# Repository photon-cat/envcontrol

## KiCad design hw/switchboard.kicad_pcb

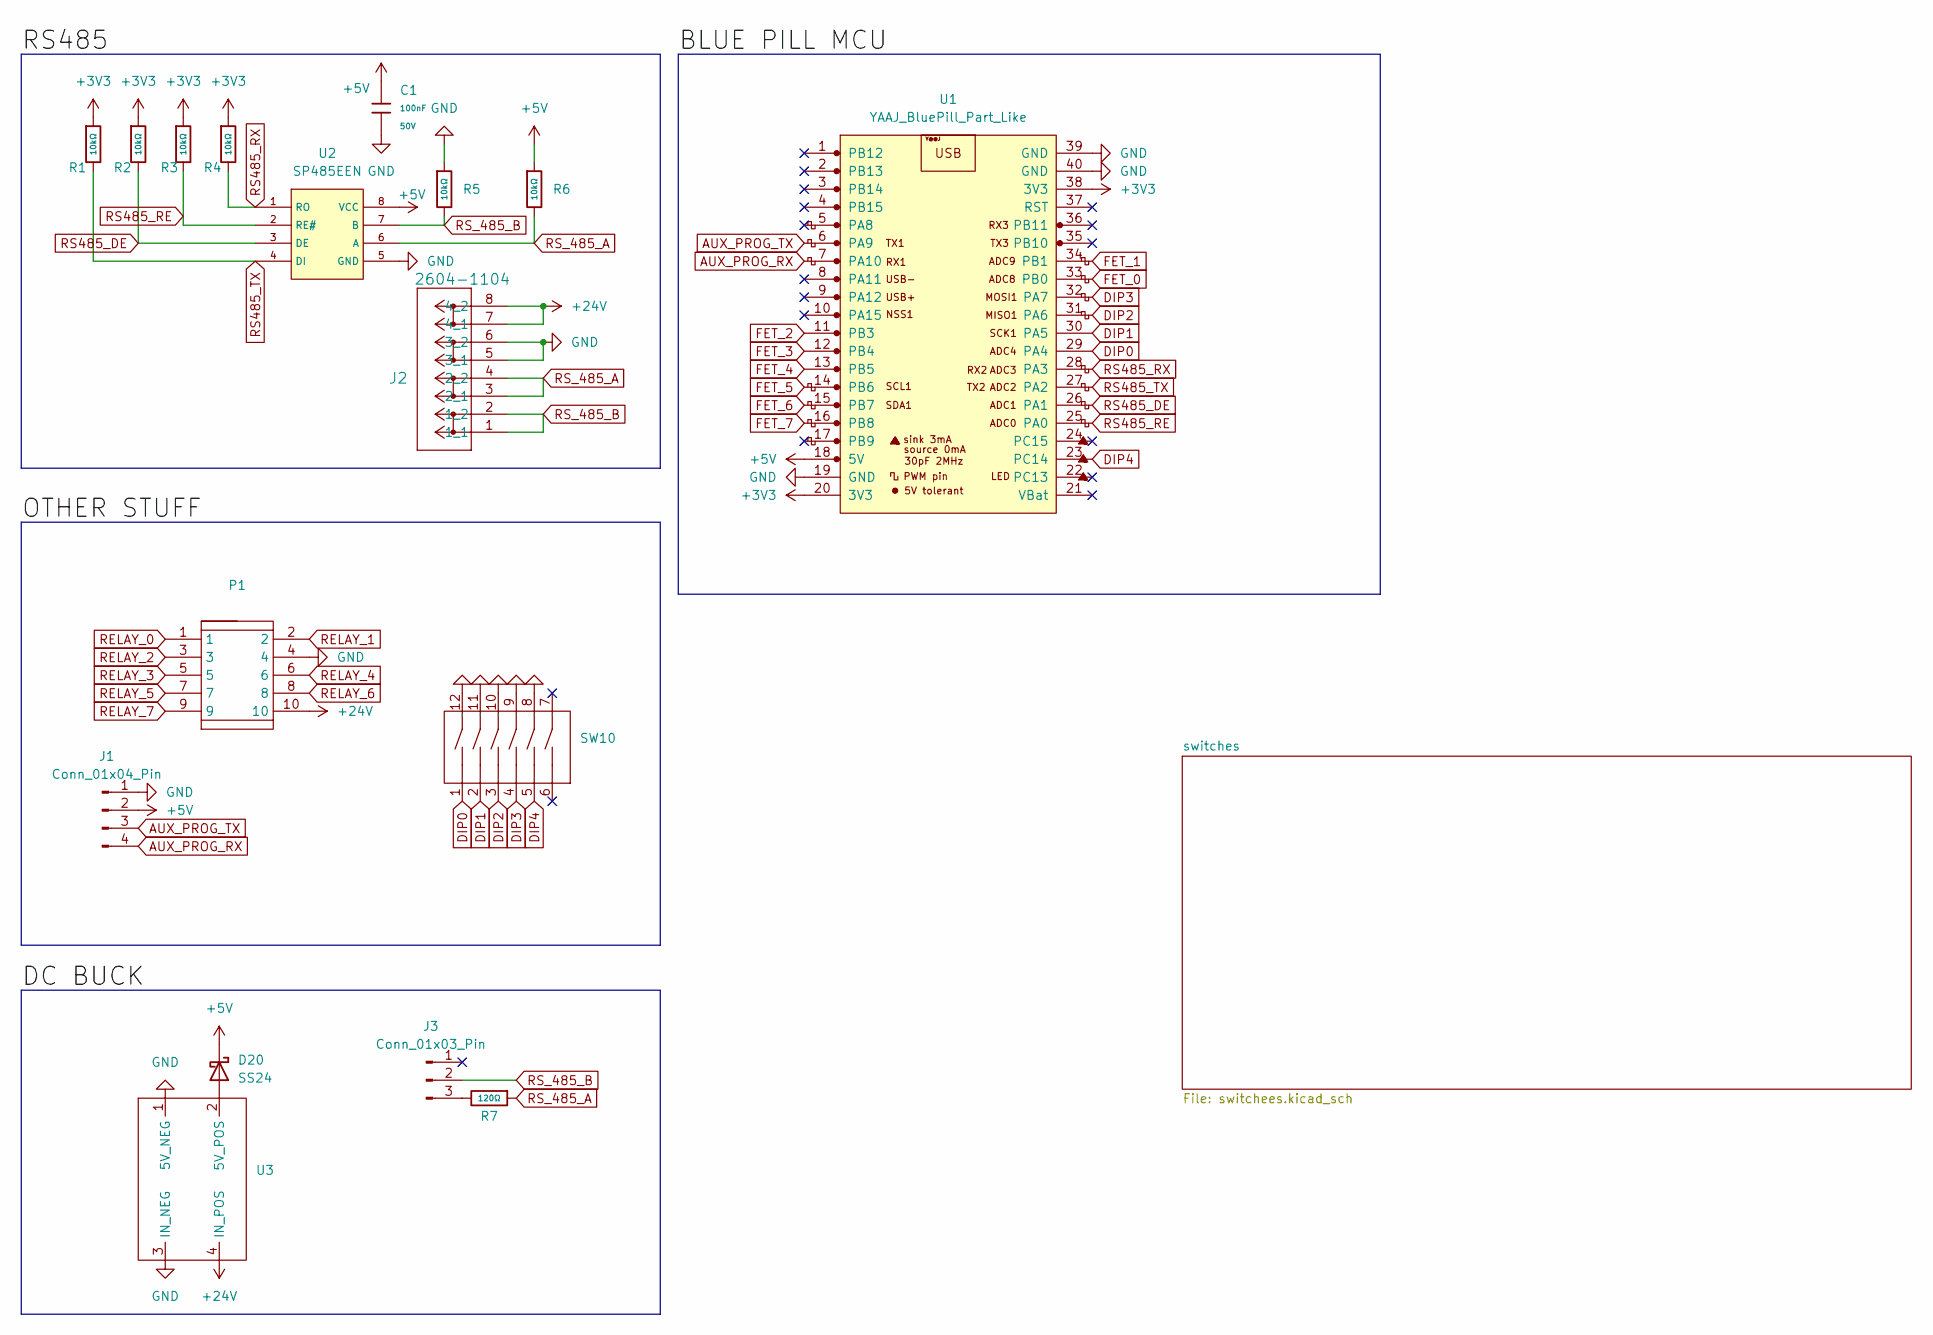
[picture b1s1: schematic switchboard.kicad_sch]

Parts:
C1: 100nF; C_0603; Voltage Rated 50V; Tolerance ±10%; Part CC0603KRX7R9BB104; LCSC C14663
D20: SS24; D_SMA
J1: Conn_01x04_Pin; PinHeader_1x04_P2.54mm_Vertical
J2: 2604-1104; CONN4_2604-1104_WAG
J3: Conn_01x03_Pin; PinHeader_1x03_P2.54mm_Horizontal
P1: IDC-TH_10P-P2.54-H-R2-C5-S2.54; Manufacturer Part 2.54-2*5P弯简牛; LCSC Part Name 2.54mm 2x5P 排数:2 每排P数:5
R1, R2, R3, R4, R5, R6: 10kΩ; R_0603; Overload Voltage (Max) 75V; Tolerance ±1%; Part 0603WAF1002T5E; LCSC C25804
R7: 120Ω; R_0603; Overload Voltage (Max) 75V; Tolerance ±1%; Part 0603WAF1200T5E; LCSC C22787
SW10: SW-TH_12P-P2.54_SMQP-06B-TP; Manufacturer Part SMQP-06B-TP; LCSC Part Name 间距2.54mm 琴键6位拨码开关
U1: YAAJ_BluePill_Part_Like; YAAJ_BluePill_1
U2: SP485EEN; SOIC-8_L5.0-W4.0-P1.27-LS6.0-BL; Supply Voltage 4.75V~5.25V; Part SP485EEN-L/TR; LCSC C6855
U3: CHINA_MP1584EN

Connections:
+3V3: R1.1, R2.1, R3.1, R4.1, U1.20 (3V3), U1.38 (3V3)
+5V: C1.1, D20.1 (K), J1.2, R6.1, U1.18 (5V), U2.8 (VCC); also elsewhere on the board
+24V: J2.7 (4_1), J2.8 (4_2), P1.10, U3.4 (IN_POS)
AUX_PROG_RX: J1.4, U1.7 (PA10)
AUX_PROG_TX: J1.3, U1.6 (PA9)
DIP0: SW10.1, U1.29 (PA4)
DIP1: SW10.2, U1.30 (PA5)
DIP2: SW10.3, U1.31 (PA6)
DIP3: SW10.4, U1.32 (PA7)
DIP4: SW10.5, U1.23 (PC14)
FET_0: U1.33 (PB0); also elsewhere on the board
FET_1: U1.34 (PB1); also elsewhere on the board
FET_2: U1.11 (PB3); also elsewhere on the board
FET_3: U1.12 (PB4); also elsewhere on the board
FET_4: U1.13 (PB5); also elsewhere on the board
FET_5: U1.14 (PB6); also elsewhere on the board
FET_6: U1.15 (PB7); also elsewhere on the board
FET_7: U1.16 (PB8); also elsewhere on the board
GND: C1.2, J1.1, J2.5 (3_1), J2.6 (3_2), P1.4, R5.1, SW10.8, SW10.9, SW10.10, SW10.11, SW10.12, U1.19 (GND), U1.39 (GND), U1.40 (GND), U2.5 (GND), U3.1 (5V_NEG), U3.3 (IN_NEG); also elsewhere on the board
unnamed: D20.2 (A), U3.2 (5V_POS)
unnamed: J3.3, R7.2
RELAY_0: P1.1; also elsewhere on the board
RELAY_1: P1.2; also elsewhere on the board
RELAY_2: P1.3; also elsewhere on the board
RELAY_3: P1.5; also elsewhere on the board
RELAY_4: P1.6; also elsewhere on the board
RELAY_5: P1.7; also elsewhere on the board
RELAY_6: P1.8; also elsewhere on the board
RELAY_7: P1.9; also elsewhere on the board
RS485_DE: R2.2, U1.26 (PA1), U2.3 (DE)
RS485_RE: R3.2, U1.25 (PA0), U2.2 (RE#)
RS485_RX: R4.2, U1.28 (PA3), U2.1 (RO)
RS485_TX: R1.2, U1.27 (PA2), U2.4 (DI)
RS_485_A: J2.3 (2_1), J2.4 (2_2), R6.2, R7.1, U2.6 (A)
RS_485_B: J2.1 (1_1), J2.2 (1_2), J3.2, R5.2, U2.7 (B)

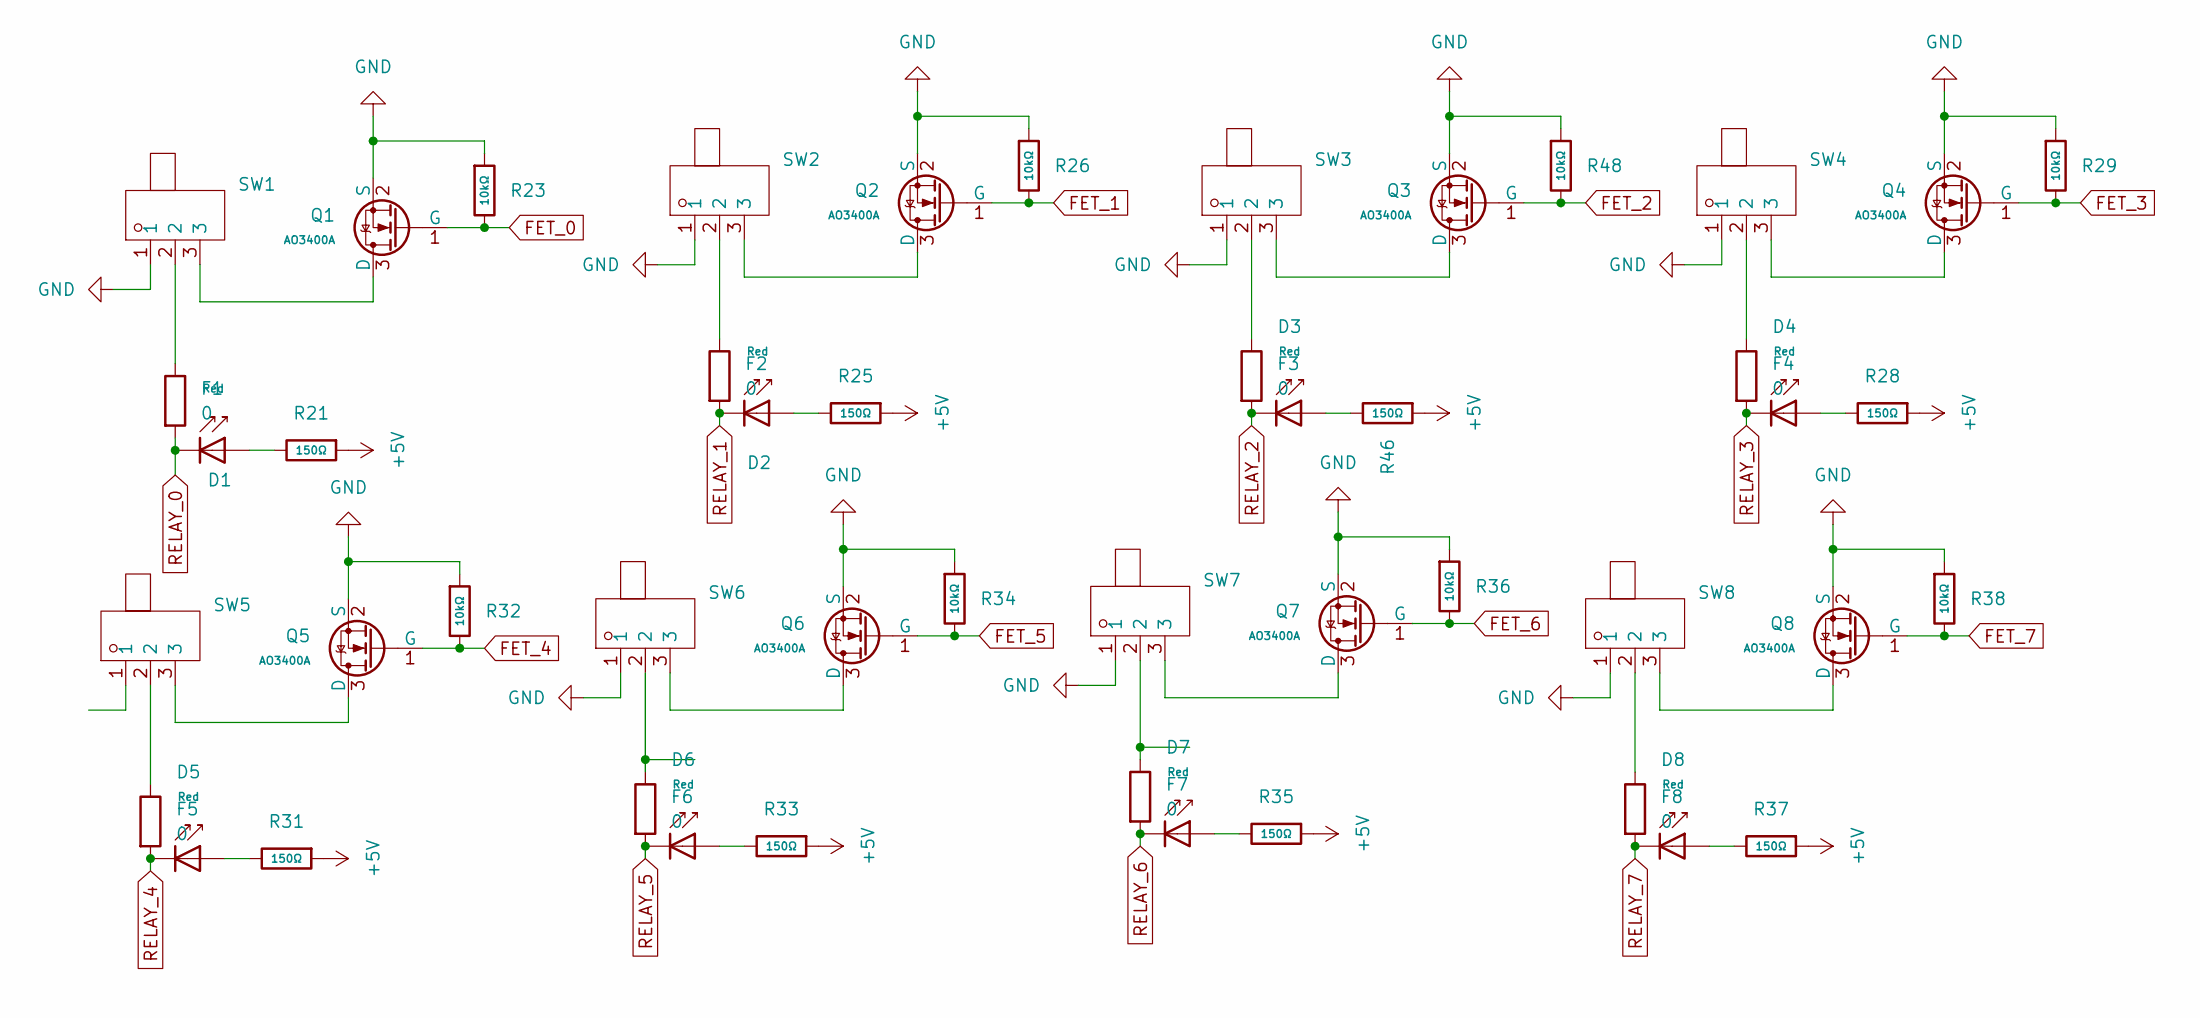
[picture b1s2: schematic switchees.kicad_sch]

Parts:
D1, D2, D3, D4, D5, D6, D7, D8: Red; D_0805; Forward Voltage (VF) 1.6V~2.6V; Part NCD0805R1; LCSC C84256
F1, F2, F3, F4, F5, F6, F7, F8: 0; R_0603
Q1, Q2, Q3, Q4, Q5, Q6, Q7, Q8: AO3400A; Q_SOT-23; Part AO3400A; LCSC C20917
R21, R25, R28, R31, R33, R35, R37, R46: 150Ω; R_0603; Overload Voltage (Max) 75V; Tolerance ±1%; Part 0603WAF1500T5E; LCSC C22808
R23, R26, R29, R32, R34, R36, R38, R48: 10kΩ; R_0603; Overload Voltage (Max) 75V; Tolerance ±1%; Part 0603WAF1002T5E; LCSC C25804
SW1, SW2, SW3, SW4, SW5, SW6, SW7, SW8: SW-TH_1MS1T1B1M1QES-5; Manufacturer Part 1MS1T1B1M1QES-5; LCSC Part Name 五件套 1MS1T1B1M1QES-5

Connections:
+5V: R21.1, R25.1, R28.1, R31.1, R33.1, R35.1, R37.1, R46.1; also elsewhere on the board
FET_0: Q1.1 (G), R23.2; also elsewhere on the board
FET_1: Q2.1 (G), R26.2; also elsewhere on the board
FET_2: Q3.1 (G), R48.2; also elsewhere on the board
FET_3: Q4.1 (G), R29.2; also elsewhere on the board
FET_4: Q5.1 (G), R32.2; also elsewhere on the board
FET_5: Q6.1 (G), R34.2; also elsewhere on the board
FET_6: Q7.1 (G), R36.2; also elsewhere on the board
FET_7: Q8.1 (G), R38.2; also elsewhere on the board
GND: Q1.2 (S), Q2.2 (S), Q3.2 (S), Q4.2 (S), Q5.2 (S), Q6.2 (S), Q7.2 (S), Q8.2 (S), R23.1, R26.1, R29.1, R32.1, R34.1, R36.1, R38.1, R48.1, SW1.1, SW2.1, SW3.1, SW4.1, SW6.1, SW7.1, SW8.1; also elsewhere on the board
unnamed: D1.2, R21.2
unnamed: D2.2, R25.2
unnamed: D3.2, R46.2
unnamed: D4.2, R28.2
unnamed: D5.2, R31.2
unnamed: D6.2, R33.2
unnamed: D7.2, R35.2
unnamed: D8.2, R37.2
unnamed: F1.1, SW1.2
unnamed: F2.1, SW2.2
unnamed: F3.1, SW3.2
unnamed: F4.1, SW4.2
unnamed: F5.1, SW5.2
unnamed: F6.1, SW6.2
unnamed: F7.1, SW7.2
unnamed: F8.1, SW8.2
unnamed: Q1.3 (D), SW1.3
unnamed: Q2.3 (D), SW2.3
unnamed: Q3.3 (D), SW3.3
unnamed: Q4.3 (D), SW4.3
unnamed: Q5.3 (D), SW5.3
unnamed: Q6.3 (D), SW6.3
unnamed: Q7.3 (D), SW7.3
unnamed: Q8.3 (D), SW8.3
RELAY_0: D1.1, F1.2; also elsewhere on the board
RELAY_1: D2.1, F2.2; also elsewhere on the board
RELAY_2: D3.1, F3.2; also elsewhere on the board
RELAY_3: D4.1, F4.2; also elsewhere on the board
RELAY_4: D5.1, F5.2; also elsewhere on the board
RELAY_5: D6.1, F6.2; also elsewhere on the board
RELAY_6: D7.1, F7.2; also elsewhere on the board
RELAY_7: D8.1, F8.2; also elsewhere on the board

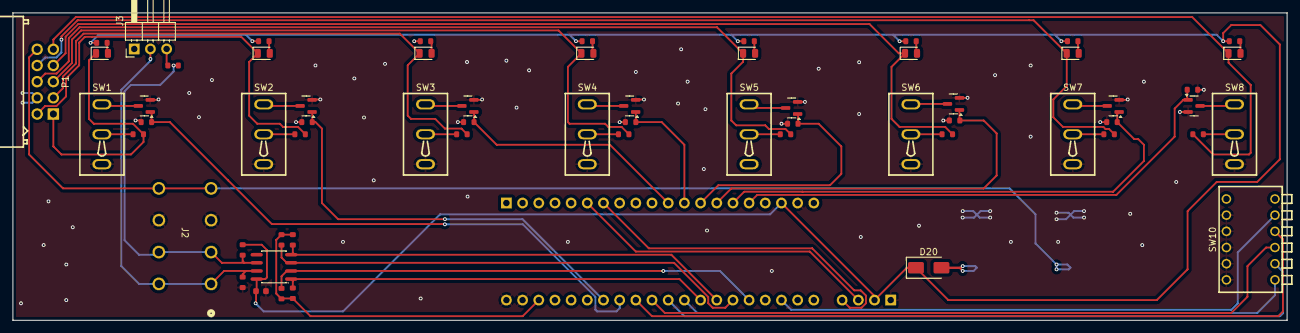
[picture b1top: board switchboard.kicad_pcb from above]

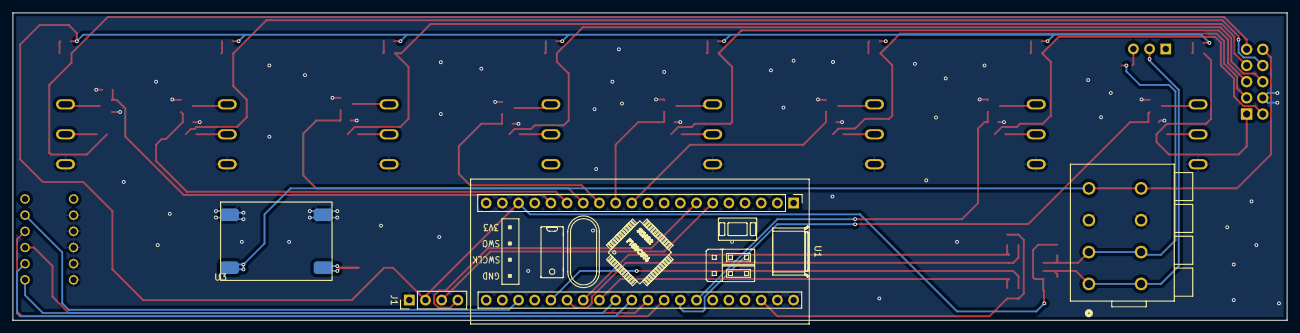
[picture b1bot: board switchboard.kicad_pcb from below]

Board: 4 copper layers, 200.0 x 48.3 mm, 65 parts (4 on the bottom side), 59 nets.

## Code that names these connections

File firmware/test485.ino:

// STM32F103 "Blue Pill" RS485 test sketch
// Configures FET outputs, DIP switch inputs, and drives RS485 at 500 kbaud.

#include <Arduino.h>

constexpr uint32_t RS485_BAUD = 500000;

// RS485 transceiver control pins
constexpr uint8_t RS485_RX_PIN = PA3;
constexpr uint8_t RS485_TX_PIN = PA2;
constexpr uint8_t RS485_DE_PIN = PA1;
constexpr uint8_t RS485_RE_PIN = PA0;  // Active low receive enable

// Some board configurations do not predefine Serial2; create it if needed.
#if !defined(HAVE_HWSERIAL2)
HardwareSerial Serial2(RS485_RX_PIN, RS485_TX_PIN);
#endif

constexpr uint8_t LED_PIN = LED_BUILTIN;  // On Blue Pill this is PC13 (active low)

// FET outputs
const uint8_t FET_PINS[] = {
  PB0,  // FET_0
  PB1,  // FET_1
  PB3,  // FET_2
  PB4,  // FET_3
  PB5,  // FET_4
  PB6,  // FET_5
  PB7,  // FET_6
  PB8   // FET_7
};

// DIP switch inputs (assumed active low to ground)
const uint8_t DIP_PINS[] = {
  PA4,  // DIP0
  PA5,  // DIP1
  PA6,  // DIP2
  PA7,  // DIP3
  PC14  // DIP4
};

void beginRs485()
{
  pinMode(RS485_DE_PIN, OUTPUT);
  pinMode(RS485_RE_PIN, OUTPUT);
  // Idle with driver enabled and receiver enabled (keeps bus driven for measurement)
  digitalWrite(RS485_DE_PIN, HIGH);
  digitalWrite(RS485_RE_PIN, LOW);

  // Make the pin selection explicit even though these are the defaults
  Serial2.setTx(RS485_TX_PIN);
  Serial2.setRx(RS485_RX_PIN);
  Serial2.begin(RS485_BAUD);
}

void sendRs485(const char *msg)
{
  // Pulse the LED while sending (active-low on PC13)
  digitalWrite(LED_PIN, LOW);

  Serial2.print(msg);
  Serial2.print("\r\n");
  Serial2.flush();

  // Keep driver asserted so A/B stay biased; receiver stays enabled
  digitalWrite(RS485_DE_PIN, HIGH);
  digitalWrite(RS485_RE_PIN, LOW);
  digitalWrite(LED_PIN, HIGH);
}

void setup()
{
  pinMode(LED_PIN, OUTPUT);
  digitalWrite(LED_PIN, HIGH);  // idle off (active-low LED)

  // Configure FET outputs and default them off
  for (uint8_t pin : FET_PINS) {
    pinMode(pin, OUTPUT);
    digitalWrite(pin, LOW);
  }

  // Configure DIP switches with pull-ups
  for (uint8_t pin : DIP_PINS) {
    pinMode(pin, INPUT_PULLUP);
  }

  beginRs485();
}

void loop()
{
  static uint32_t lastTx = 0;
  const uint32_t now = millis();

  if (now - lastTx >= 200) {  // 5 Hz
    lastTx = now;
    sendRs485("RS485 test message @500000 baud");
  }
}

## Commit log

2025-11-11 first
2025-11-13 add ct interface
2025-11-13 Add CT interface protocol library and docs
